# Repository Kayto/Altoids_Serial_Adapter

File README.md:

# Altoids Serial Adapter

**Latest News**

* **DESIGN IN PROGRESS. UNTESTED**

## Introduction

Fed up with having to use multiple USB serial adapters and wiring configurations? Just want to plug in and go. This project was born from a desire for a quick and neat way to interface with various single board homebrew computers (SBCs)- such as the Kim-Uno, Southern Cross and SC131 to name a few. Most USB serial adapters are bare boards, have tiny pin labels and come with different logic voltages and pin out orders. This makes it a fiddle to set up. What power, what logic, mess around switching dupont jumper cables between the correct pins....
With the Altoid Serial Adapter the fiddle is over. You're welcome!

## Credits and thanks

Credits and thanks are worthy of being up front.

* **Lee Hart** for inspiring the look and feel of this project. Please check out his site for some amazing SBCs. https://www.sunrise-ev.com/index.htm
* Tom Van Baak for the brilliant picDIV™ project. Please check out his site for all things clock.
* bborncr for the initial PCB outline and sizing to fit the Altoids tin. https://github.com/bborncr/AltoidsPCB
* FTDI 

## General Aims

* Provide 'plug and play' connections using fixed ribbon cables for the most typical serial pin connection order. I don't want to be crossing wires and tracing wire colours.
* Provide some nice LEDs.
* Switchable power and serial logic voltages.
* Fit it all to look nice and tidy in an Altoids tin.
* For ease, safety and to simplify both design and assembly (and probably cost) use commercially available modules for the power regulation, multiplexing and charging.
* Limit the SMD to ease assembly.

## Bespoke Aims

These are added features that suit more bespoke applications.

* SBCs such as the Kim-Uno and Membership Cards dont always warrant a serial connection as they can be programmed by switches and buttons. Therefore why not provide some onboard battery power.
* With an onboard battery, may as well be able to charge it.
* As we have regulated power we may as well break it out - to be useful for other things.
* Sometimes you may need a signal High or Low? My use is that some SBCs need a High or Low to activate a display. Provide a switch for that, i like switches.
* Ok, the serial adapter IC has an onboard oscillator. It would be a shame to waste that. Wait, the oscillator runs at 2024 speeds, i need something slower for 1980s tech. Use a PIC to divide the clock and provide a breakout for sub 6MHZ clock signals. Might come in handy.
* For the clock, provide breakouts for onboard PIC programming. This then offers more possibilities without having to disassemble the board.

## Final Features

In no particular order the main features in the final board are as follows.

- Programmable clock breakout using the picDIV™ project.
- Indicator LEDs for the main functions and configurations.
- Onboard Li-ion battery charger.
- Selectable 5V and 3V3 power and logic.
- Seperate Power breakout.
- High and Low signal logic breakout

## Build

Coming Soon.

### REVISION STATUS & ISSUES
**REV 000**
* DRAFT DESIGN IN PRODUCTION. UNTESTED AT THE MOMENT.

## Firmware

Comming soon.
Instructions for the FT232R clock configuration.
Instructions for the picDIV™ project.

## Licenses & acknowledgement
Further to the links in the credit section.

**KiCad Library**

**picDIV™**
http://www.leapsecond.com/pic/
http://www.leapsecond.com/pic/src/readme

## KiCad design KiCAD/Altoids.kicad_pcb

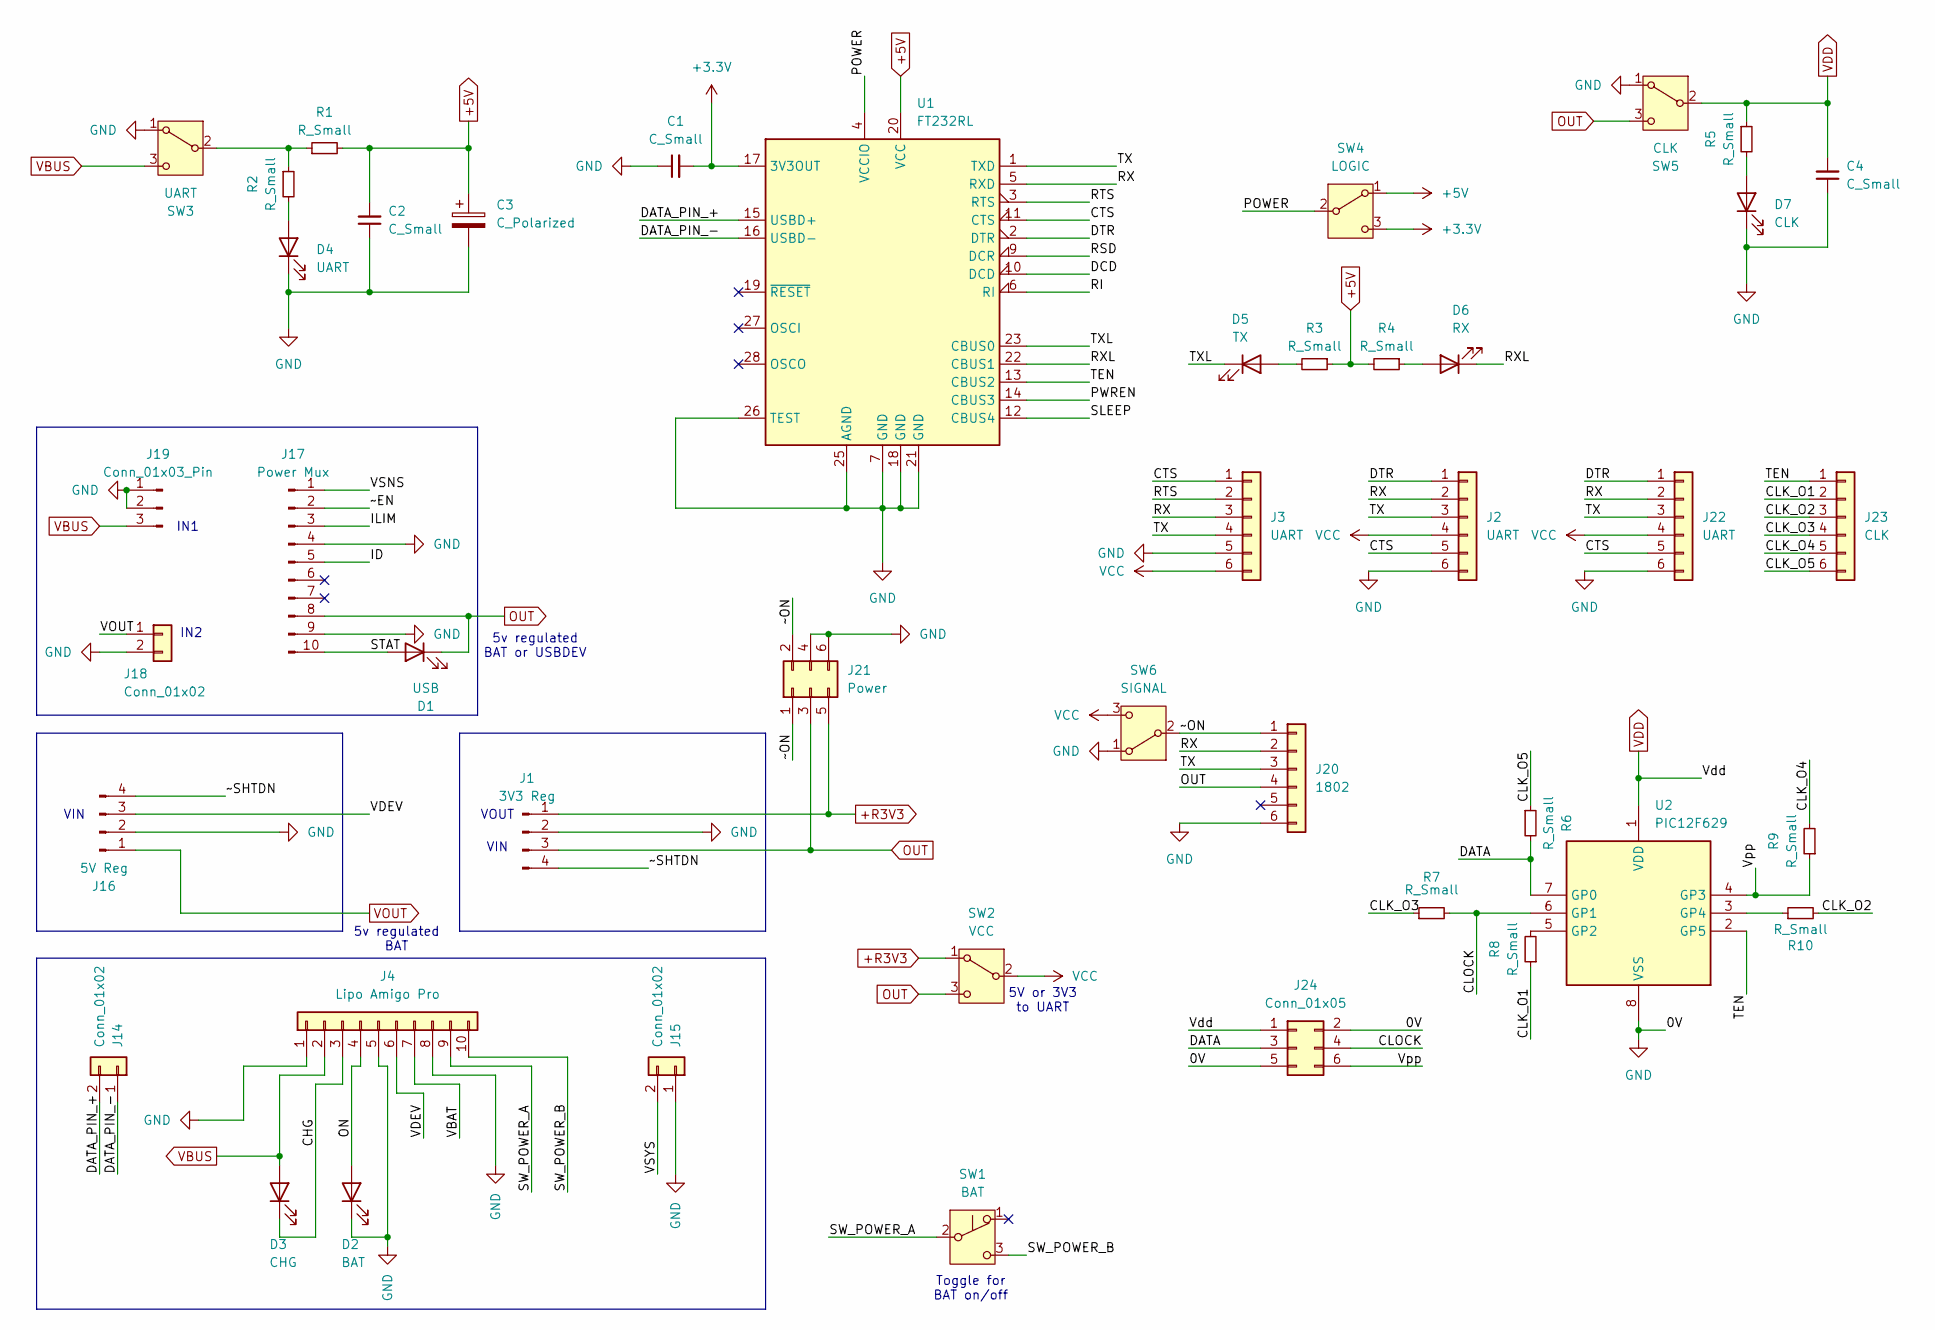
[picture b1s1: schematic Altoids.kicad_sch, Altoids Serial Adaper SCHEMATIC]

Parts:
C1, C2, C4: C_Small; C_1206_3216Metric_Pad1.33x1.80mm_HandSolder
C3: C_Polarized; C_1206_3216Metric_Pad1.33x1.80mm_HandSolder
D1: USB; LED_D3.0mm
D2: BAT; LED_D3.0mm
D3: CHG; LED_D3.0mm
D4: UART; LED_D3.0mm
D5: TX; LED_D3.0mm
D6: RX; LED_D3.0mm
D7: CLK; LED_D3.0mm
J1: 3V3 Reg; PinHeader_1x04_P2.54mm_Vertical_no_PINS
J2, J3, J22: UART; PinHeader_1x06_P2.54mm_Vertical
J4: Lipo Amigo Pro; PinHeader_1x10_P2.54mm_Vertical
J14, J15, J18: Conn_01x02; PinHeader_1x02_P2.54mm_Vertical_no_PINS
J16: 5V Reg; PinHeader_1x04_P2.54mm_Vertical_no_PINS
J17: Power Mux; PinHeader_1x10_P2.54mm_Vertical_no_PINS
J19: Conn_01x03_Pin; PinHeader_1x03_P2.54mm_Vertical_no_PINS
J20: 1802; PinHeader_1x06_P2.54mm_Vertical
J21: Power; PinHeader_2x03_P2.54mm_Vertical
J23: CLK; PinHeader_1x06_P2.54mm_Vertical
J24: Conn_01x05; PinHeader_2x03_P2.54mm_Vertical
R1, R2, R3, R4, R5, R6, R7, R8, R9, R10: R_Small; R_0805_2012Metric
SW1: BAT; SW_Toggle_Blue_wSlots
SW2: VCC; SW_Toggle_Blue_wSlots
SW3: UART; SW_Toggle_Blue_wSlots
SW4: LOGIC; SW_Toggle_Blue_wSlots
SW5: CLK; SW_Toggle_Blue_wSlots
SW6: SIGNAL; SW_Toggle_Blue_wSlots
U1: FT232RL; SSOP-28_5.3x10.2mm_P0.65mm
U2: PIC12F629; DIP-8_W7.62mm

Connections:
+3.3V: C1.2, SW4.3 (C), U1.17 (3V3OUT)
+5V: C2.2, C3.1, R1.2, R3.1, R4.2, SW4.1 (A), U1.20 (VCC)
+R3V3: J1.1, J21.5, SW2.1 (A)
/CHG: D3.1 (K), J4.3
/CLK_O1: J23.2, R8.1
/CLK_O2: J23.3, R10.2
/CLK_O3: J23.4, R7.1
/CLK_O4: J23.5, R9.2
/CLK_O5: J23.6, R6.1
/CLOCK: J24.4, R7.2, U2.6 (GP1)
/CTS: J2.5, J3.1, J22.5, U1.11 (CTS)
/DATA: J24.3, R6.2, U2.7 (GP0)
/DATA_PIN_+: J14.2, U1.15 (USBD+)
/DATA_PIN_-: J14.1, U1.16 (USBD-)
/DCD: U1.10 (DCD)
/DTR: J2.1, J22.1, U1.2 (DTR)
/ID: J17.5
/ILIM: J17.3
/ON: D2.2 (A), J4.4
/POWER: SW4.2 (B), U1.4 (VCCIO)
/PWREN: U1.14 (CBUS3)
/RI: U1.6 (RI)
/RSD: U1.9 (DCR)
/RTS: J3.2, U1.3 (RTS)
/RX: J2.2, J3.3, J20.2, J22.2, U1.5 (RXD)
/RXL: D6.1 (K), U1.22 (CBUS1)
/SLEEP: U1.12 (CBUS4)
/STAT: D1.2 (A), J17.10
/SW_POWER_A: J4.9, SW1.2 (B)
/SW_POWER_B: J4.10, SW1.3 (C)
/TEN: J23.1, U1.13 (CBUS2), U2.2 (GP5)
/TX: J2.3, J3.4, J20.3, J22.3, U1.1 (TXD)
/TXL: D5.1 (K), U1.23 (CBUS0)
/VBAT: J4.7
/VDEV: J4.6, J16.3
/VSNS: J17.1
/VSYS: J15.2
/Vpp: J24.6, R9.1, U2.4 (GP3)
/~EN: J17.2
/~ON: J20.1, J21.1, J21.2, SW6.2 (B)
/~SHTDN: J1.4, J16.4
GND: C1.1, C2.1, C3.2, C4.1, D2.1 (K), D4.1 (K), D7.1 (K), J1.2, J2.6, J3.5, J4.1, J4.5, J4.8, J15.1, J16.2, J17.4, J17.9, J18.2, J19.1, J19.2, J20.6, J21.4, J21.6, J22.6, J24.2, J24.5, SW3.1 (A), SW5.1 (A), SW6.1 (A), U1.7 (GND), U1.18 (GND), U1.21 (GND), U1.25 (AGND), U1.26 (TEST), U2.8 (VSS)
unnamed: D4.2 (A), R2.2
unnamed: D5.2 (A), R3.2
unnamed: D6.2 (A), R4.1
unnamed: D7.2 (A), R5.2
unnamed: R1.1, R2.1, SW3.2 (B)
unnamed: R8.2, U2.5 (GP2)
unnamed: R10.1, U2.3 (GP4)
OUT: D1.1 (K), J1.3, J17.8, J20.4, J21.3, SW2.3 (C), SW5.3 (C)
VBUS: D3.2 (A), J4.2, J19.3, SW3.3 (C)
VCC: J2.4, J3.6, J22.4, SW2.2 (B), SW6.3 (C)
VDD: C4.2, J24.1, R5.1, SW5.2 (B), U2.1 (VDD)
VOUT: J16.1, J18.1

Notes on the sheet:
VOUT
Toggle for BAT on/off
5V or 3V3 to UART
5v regulated BAT
VIN
IN1
5v regulated BAT or USBDEV
IN2

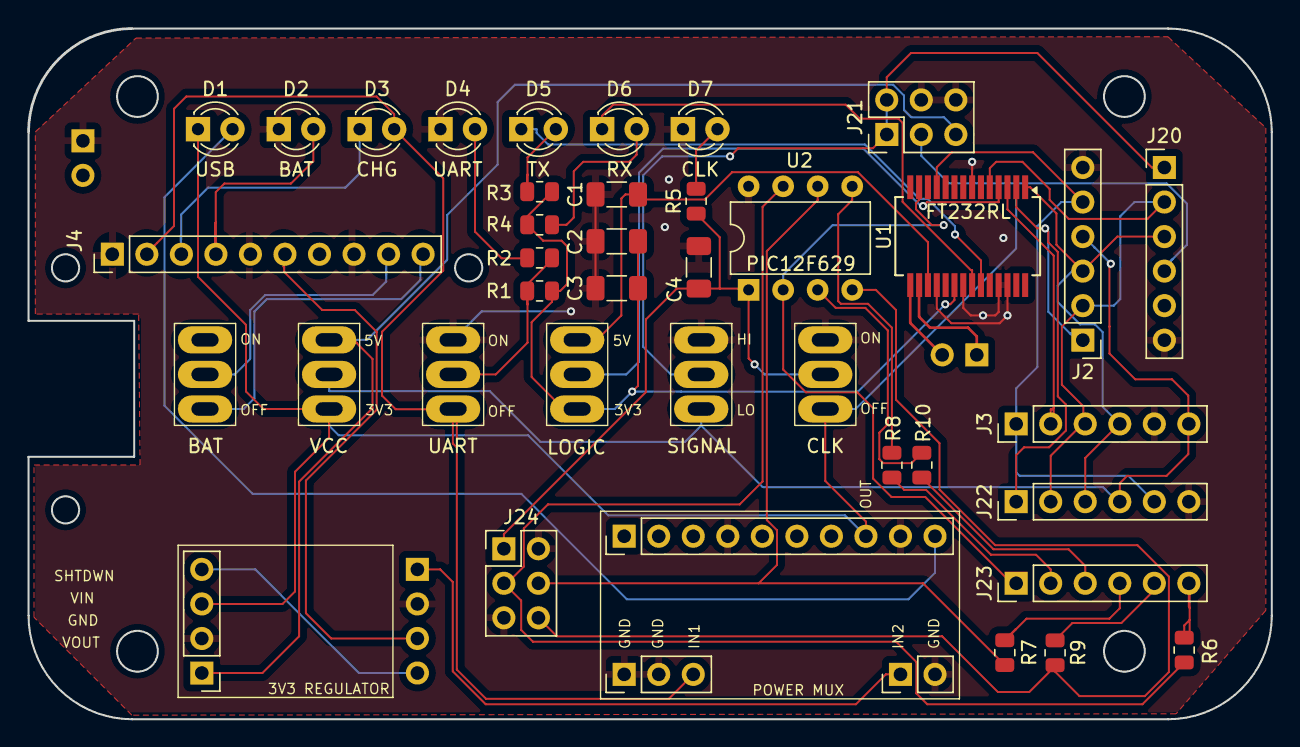
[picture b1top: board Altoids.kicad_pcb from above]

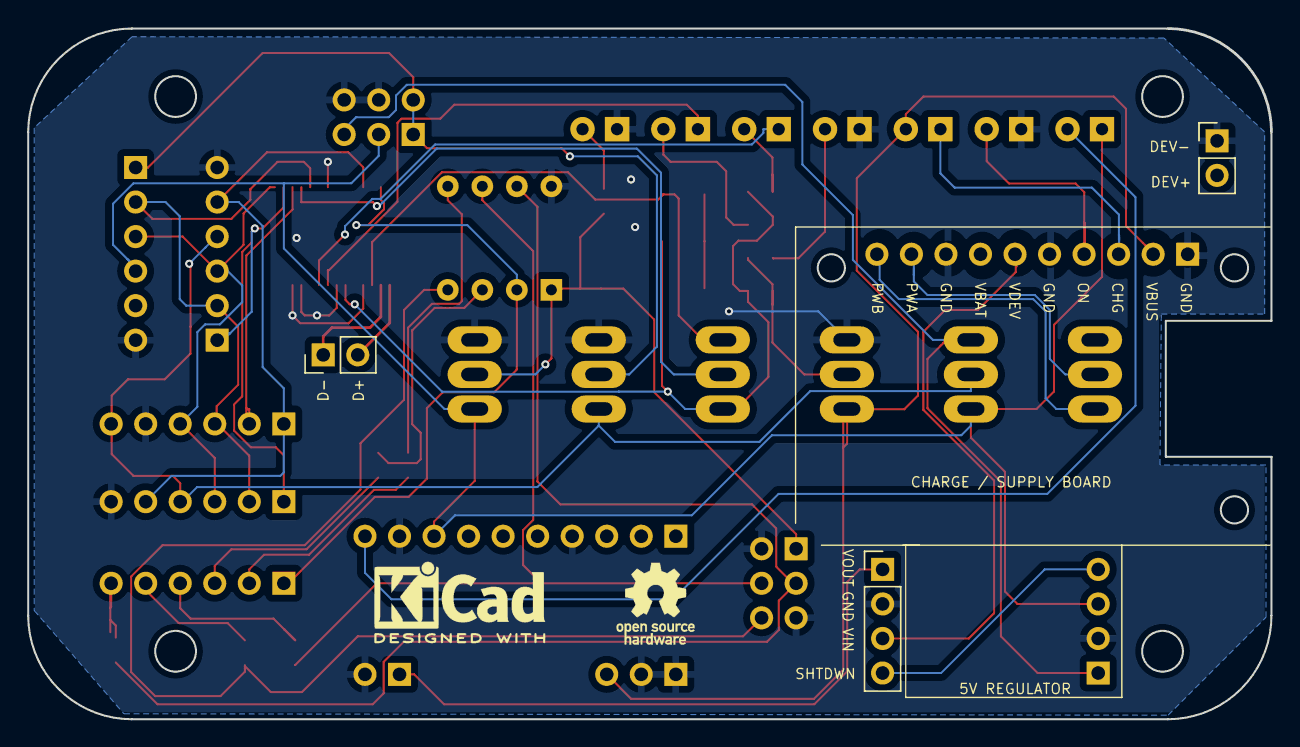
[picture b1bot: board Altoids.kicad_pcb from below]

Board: 2 copper layers, 91.4 x 50.8 mm, 44 parts (3 on the bottom side), 43 nets.
